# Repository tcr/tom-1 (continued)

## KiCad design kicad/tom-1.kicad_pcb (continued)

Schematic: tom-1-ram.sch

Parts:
J6: Conn_02x08_Top_Bottom; PinSocket_2x09_P2.54mm_Vertical
U22, U28: CY62256; DIP-28_W15.24mm

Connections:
/ADD/stack0: U22.21 (A0); also elsewhere on the board
/ADD/stack1: U22.23 (A1); also elsewhere on the board
/ADD/stack2: U22.24 (A2); also elsewhere on the board
/ADD/stack3: U22.25 (A3); also elsewhere on the board
/ADD/stack4: U22.26 (A4); also elsewhere on the board
/ADD/stack5: U22.1 (A5); also elsewhere on the board
/ADD/stack6: U22.2 (A6); also elsewhere on the board
/ADD/stack7: U22.3 (A7); also elsewhere on the board
/ADD/stack8: U22.4 (A8); also elsewhere on the board
/ADD/stack9: U22.5 (A9); also elsewhere on the board
/ADD/stack10: U22.6 (A10); also elsewhere on the board
/ADD/stack11: U22.7 (A11); also elsewhere on the board
/ADD/stack12: U22.8 (A12); also elsewhere on the board
/ADD/stack13: U22.9 (A13); also elsewhere on the board
/ADD/stack14: U22.10 (A14); also elsewhere on the board
/ADD/tos_bus0: U22.11 (D0); also elsewhere on the board
/ADD/tos_bus1: U22.12 (D1); also elsewhere on the board
/ADD/tos_bus2: U22.13 (D2); also elsewhere on the board
/ADD/tos_bus3: U22.15 (D3); also elsewhere on the board
/ADD/tos_bus4: U22.16 (D4); also elsewhere on the board
/ADD/tos_bus5: U22.17 (D5); also elsewhere on the board
/ADD/tos_bus6: U22.18 (D6); also elsewhere on the board
/ADD/tos_bus7: U22.19 (D7); also elsewhere on the board
/ADD/tos_bus8: U28.11 (D0); also elsewhere on the board
/ADD/tos_bus9: U28.12 (D1); also elsewhere on the board
/ADD/tos_bus10: U28.13 (D2); also elsewhere on the board
/ADD/tos_bus11: U28.15 (D3); also elsewhere on the board
/ADD/tos_bus12: U28.16 (D4); also elsewhere on the board
/ADD/tos_bus13: U28.17 (D5); also elsewhere on the board
/ADD/tos_bus14: U28.18 (D6); also elsewhere on the board
/ADD/tos_bus15: U28.19 (D7); also elsewhere on the board
/RAM/~chip_enable: U28.20 (~CE)
/RAM/~chip_enable~: U22.20 (~CE)
/RAM/~output_enable~: U22.22 (~OE), U28.22 (~OE)
/RAM/~write_enable~: U22.27 (~WE), U28.27 (~WE)
GNDREF: U22.14 (VSS), U28.14 (VSS); also elsewhere on the board
VCC: U22.28 (VCC), U28.28 (VCC); also elsewhere on the board

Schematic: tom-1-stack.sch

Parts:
J8: Conn_02x08_Top_Bottom; PinSocket_2x09_P2.54mm_Vertical
U10, U11: 2KB_SRAM; DIP-24_W10.16mm

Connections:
/ADD/stack0: U10.9 (D0); also elsewhere on the board
/ADD/stack1: U10.10 (D1); also elsewhere on the board
/ADD/stack2: U10.11 (D2); also elsewhere on the board
/ADD/stack3: U10.13 (D3); also elsewhere on the board
/ADD/stack4: U10.14 (D4); also elsewhere on the board
/ADD/stack5: U10.15 (D5); also elsewhere on the board
/ADD/stack6: U10.16 (D6); also elsewhere on the board
/ADD/stack7: U10.17 (D7); also elsewhere on the board
/ADD/stack8: U11.9 (D0); also elsewhere on the board
/ADD/stack9: U11.10 (D1); also elsewhere on the board
/ADD/stack10: U11.11 (D2); also elsewhere on the board
/ADD/stack11: U11.13 (D3); also elsewhere on the board
/ADD/stack12: U11.14 (D4); also elsewhere on the board
/ADD/stack13: U11.15 (D5); also elsewhere on the board
/ADD/stack14: U11.16 (D6); also elsewhere on the board
/ADD/stack15: U11.17 (D7); also elsewhere on the board
/D/R Registers/stack0: U10.8 (A0), U11.8 (A0); also elsewhere on the board
/D/R Registers/stack1: U10.7 (A1), U11.7 (A1); also elsewhere on the board
/D/R Registers/stack2: U10.6 (A2), U11.6 (A2); also elsewhere on the board
/D/R Registers/stack3: U10.5 (A3~), U11.5 (A3~)
/D/R Registers/stack4: U10.4 (A4~), U11.4 (A4~); also elsewhere on the board
/D/R Registers/stack5: U10.3 (A5~), U11.3 (A5~); also elsewhere on the board
/D/R Registers/stack6: U10.2 (A6~), U11.2 (A6~); also elsewhere on the board
/D/R Registers/stack7: U10.1 (A7), U11.1 (A7)
/Stack/a8: U10.23 (A8), U11.23 (A8)
/Stack/~chip_select: U10.18 (~CS), U11.18 (~CS)
/Stack/~output_enable: U10.20 (~OE), U11.20 (~OE)
/Stack/~write_enable: U10.21 (~WE), U11.21 (~WE)
GNDREF: U10.12 (GND~), U10.19 (A10), U10.22 (A9), U11.12 (GND~), U11.19 (A10), U11.22 (A9); also elsewhere on the board
VCC: U10.24 (VCC), U11.24 (VCC); also elsewhere on the board

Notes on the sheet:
STACK: SRAM (2K x 16) with 1.5K unused

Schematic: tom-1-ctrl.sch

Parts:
U4: 74LS573; DIP-20_W7.62mm

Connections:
/Control/output_enable: U4.1 (OE)
/TOS/clk: U4.11 (Load); also elsewhere on the board
GND: U4.10 (GND); also elsewhere on the board
VCC: U4.20 (VCC); also elsewhere on the board

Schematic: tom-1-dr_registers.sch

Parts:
IC4: 74HC697; DIP-20_W7.62mm
J5: Conn_02x08_Top_Bottom; PinSocket_2x09_P2.54mm_Vertical
U6, U16, U17: 74LS697; DIP-20_W7.62mm

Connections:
/D/R Registers/stack0: IC4.18 (QA), U16.18 (QA); also elsewhere on the board
/D/R Registers/stack1: IC4.17 (QB), U16.17 (QB); also elsewhere on the board
/D/R Registers/stack2: IC4.16 (QC), U16.16 (QC); also elsewhere on the board
/D/R Registers/stack4: U6.18 (QA), U17.18 (QA); also elsewhere on the board
/D/R Registers/stack5: U6.17 (QB), U17.17 (QB); also elsewhere on the board
/D/R Registers/stack6: U6.16 (QC), U17.16 (QC); also elsewhere on the board
/D/R Registers/~d_enable: IC4.7 (~ENP), U6.7 (~ENP)
/D/R Registers/~r_enable: U16.7 (~ENP), U17.7 (~ENP)
GNDREF: IC4.10 (GND), U6.10 (GND), U17.10 (GND); also elsewhere on the board
VCC: IC4.13 (~LOAD), IC4.20 (VCC), U6.13 (~LOAD), U6.20 (VCC), U16.13 (~LOAD), U16.20 (VCC), U17.13 (~LOAD), U17.20 (VCC); also elsewhere on the board

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
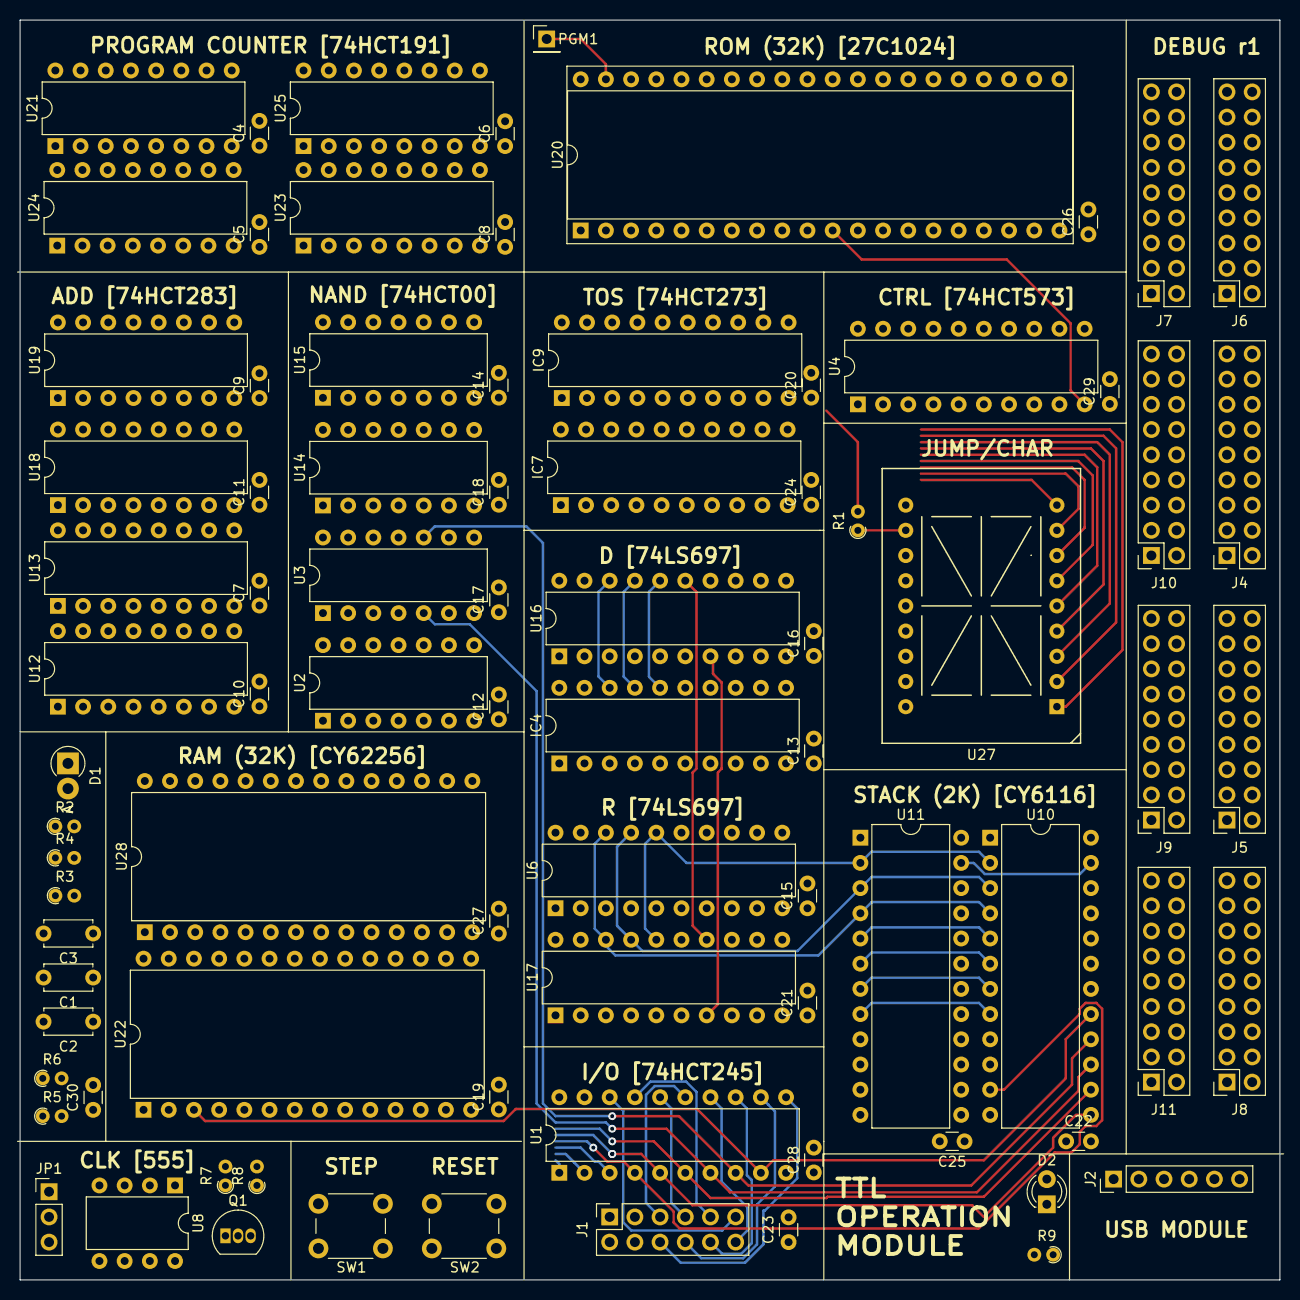
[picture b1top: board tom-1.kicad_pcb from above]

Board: 4 copper layers, 127.0 x 127.0 mm, 83 parts (0 on the bottom side), 132 nets.

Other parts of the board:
PGM1: Conn_01x01_Male; PinHeader_1x01_P2.54mm_Vertical

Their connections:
unnamed 282: PGM1.1; also elsewhere on the board

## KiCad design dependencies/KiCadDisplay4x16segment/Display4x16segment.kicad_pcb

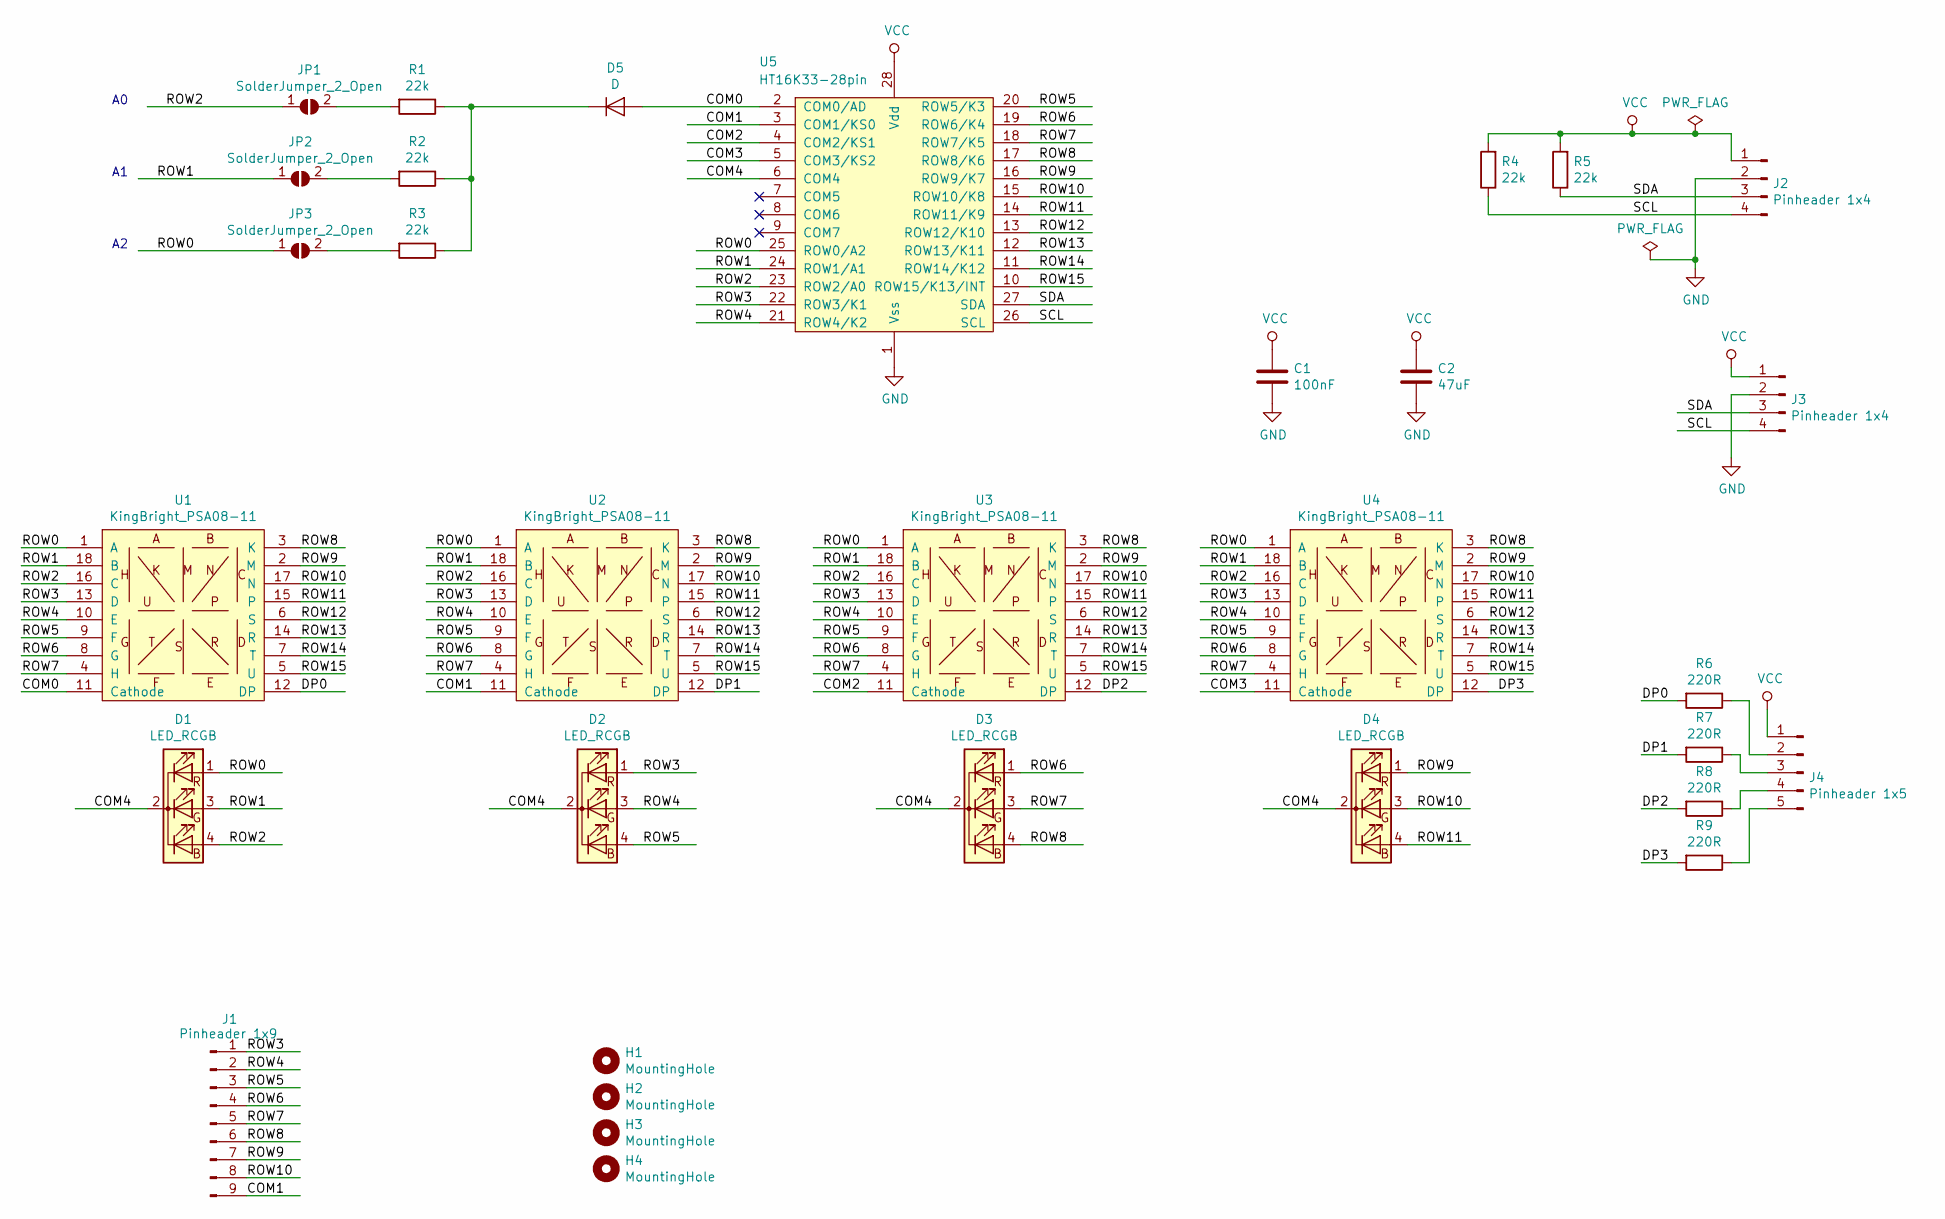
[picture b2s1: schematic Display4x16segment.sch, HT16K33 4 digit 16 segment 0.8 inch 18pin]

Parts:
C1: 100nF; C_0805_HandSoldering
C2: 47uF; C_1206_HandSoldering
D1, D2, D3, D4: LED_RCGB; LED_D5.0mm-4
D5: D; D_SOD-323_HandSoldering
H1, H2, H3, H4: MountingHole; MountingHole_2.2mm_M2_DIN965
J1: Pinheader 1x9; Pin_Header_Straight_1x09_Pitch2.54mm
J2, J3: Pinheader 1x4; Pin_Header_Straight_1x04_Pitch2.54mm
J4: Pinheader 1x5; Pin_Header_Straight_1x05_Pitch2.54mm
JP1, JP2, JP3: SolderJumper_2_Open; SolderJumper-2_P1.3mm_Open_RoundedPad1.0x1.5mm
R1, R2, R3, R4, R5: 22k; R_0805_HandSoldering
R6, R7, R8, R9: 220R; R_0805_HandSoldering
U1, U2, U3, U4: KingBright_PSA08-11; Display08inch16segment
U5: HT16K33-28pin; SOIC-28W_7.5x18.7mm_Pitch1.27mm

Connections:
/COM0: D5.2 (A), U1.11 (Cathode), U5.2 (COM0/AD)
/COM1: J1.9, U2.11 (Cathode), U5.3 (COM1/KS0)
/COM2: U3.11 (Cathode), U5.4 (COM2/KS1)
/COM3: U4.11 (Cathode), U5.5 (COM3/KS2)
/COM4: D1.2 (K), D2.2 (K), D3.2 (K), D4.2 (K), U5.6 (COM4)
/DP0: R6.2, U1.12 (DP)
/DP1: R7.2, U2.12 (DP)
/DP2: R8.2, U3.12 (DP)
/DP3: R9.2, U4.12 (DP)
/ROW0: D1.1 (RA), JP3.1 (A), U1.1 (A), U2.1 (A), U3.1 (A), U4.1 (A), U5.25 (ROW0/A2)
/ROW1: D1.3 (GA), JP2.1 (A), U1.18 (B), U2.18 (B), U3.18 (B), U4.18 (B), U5.24 (ROW1/A1)
/ROW2: D1.4 (BA), JP1.1 (A), U1.16 (C), U2.16 (C), U3.16 (C), U4.16 (C), U5.23 (ROW2/A0)
/ROW3: D2.1 (RA), J1.1, U1.13 (D), U2.13 (D), U3.13 (D), U4.13 (D), U5.22 (ROW3/K1)
/ROW4: D2.3 (GA), J1.2, U1.10 (E), U2.10 (E), U3.10 (E), U4.10 (E), U5.21 (ROW4/K2)
/ROW5: D2.4 (BA), J1.3, U1.9 (F), U2.9 (F), U3.9 (F), U4.9 (F), U5.20 (ROW5/K3)
/ROW6: D3.1 (RA), J1.4, U1.8 (G), U2.8 (G), U3.8 (G), U4.8 (G), U5.19 (ROW6/K4)
/ROW7: D3.3 (GA), J1.5, U1.4 (H), U2.4 (H), U3.4 (H), U4.4 (H), U5.18 (ROW7/K5)
/ROW8: D3.4 (BA), J1.6, U1.3 (K), U2.3 (K), U3.3 (K), U4.3 (K), U5.17 (ROW8/K6)
/ROW9: D4.1 (RA), J1.7, U1.2 (M), U2.2 (M), U3.2 (M), U4.2 (M), U5.16 (ROW9/K7)
/ROW10: D4.3 (GA), J1.8, U1.17 (N), U2.17 (N), U3.17 (N), U4.17 (N), U5.15 (ROW10/K8)
/ROW11: D4.4 (BA), U1.15, U2.15, U3.15, U4.15, U5.14 (ROW11/K9)
/ROW12: U1.6 (S), U2.6 (S), U3.6 (S), U4.6 (S), U5.13 (ROW12/K10)
/ROW13: U1.14 (R), U2.14 (R), U3.14 (R), U4.14 (R), U5.12 (ROW13/K11)
/ROW14: U1.7 (T), U2.7 (T), U3.7 (T), U4.7 (T), U5.11 (ROW14/K12)
/ROW15: U1.5 (U), U2.5 (U), U3.5 (U), U4.5 (U), U5.10 (ROW15/K13/INT)
/SCL: J2.4, J3.4, R4.1, U5.26 (SCL)
/SDA: J2.3, J3.3, R5.1, U5.27 (SDA)
GND: C1.2, C2.2, J2.2, J3.2, U5.1 (Vss)
unnamed: D5.1 (K), R1.1, R2.1, R3.1
unnamed: J4.2, R6.1
unnamed: J4.3, R7.1
unnamed: J4.4, R8.1
unnamed: J4.5, R9.1
unnamed: JP1.2 (B), R1.2
unnamed: JP2.2 (B), R2.2
unnamed: JP3.2 (B), R3.2
VCC: C1.1, C2.1, J2.1, J3.1, J4.1, R4.2, R5.2, U5.28 (Vdd)

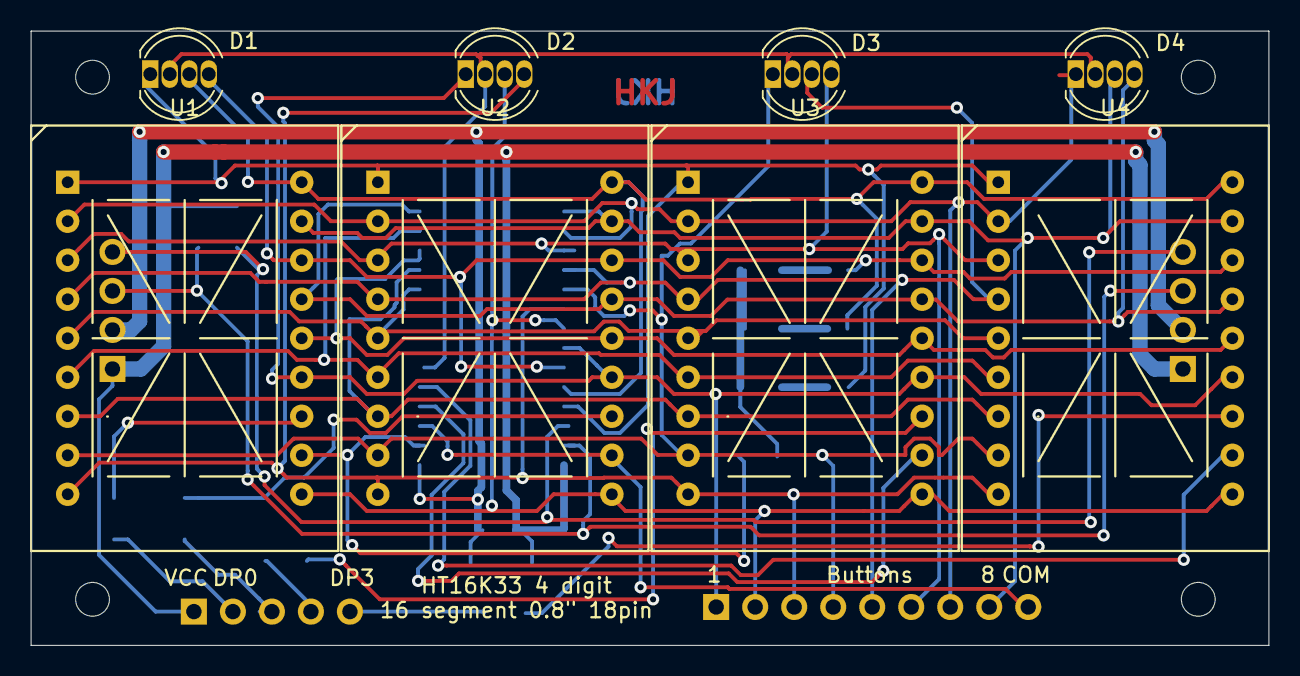
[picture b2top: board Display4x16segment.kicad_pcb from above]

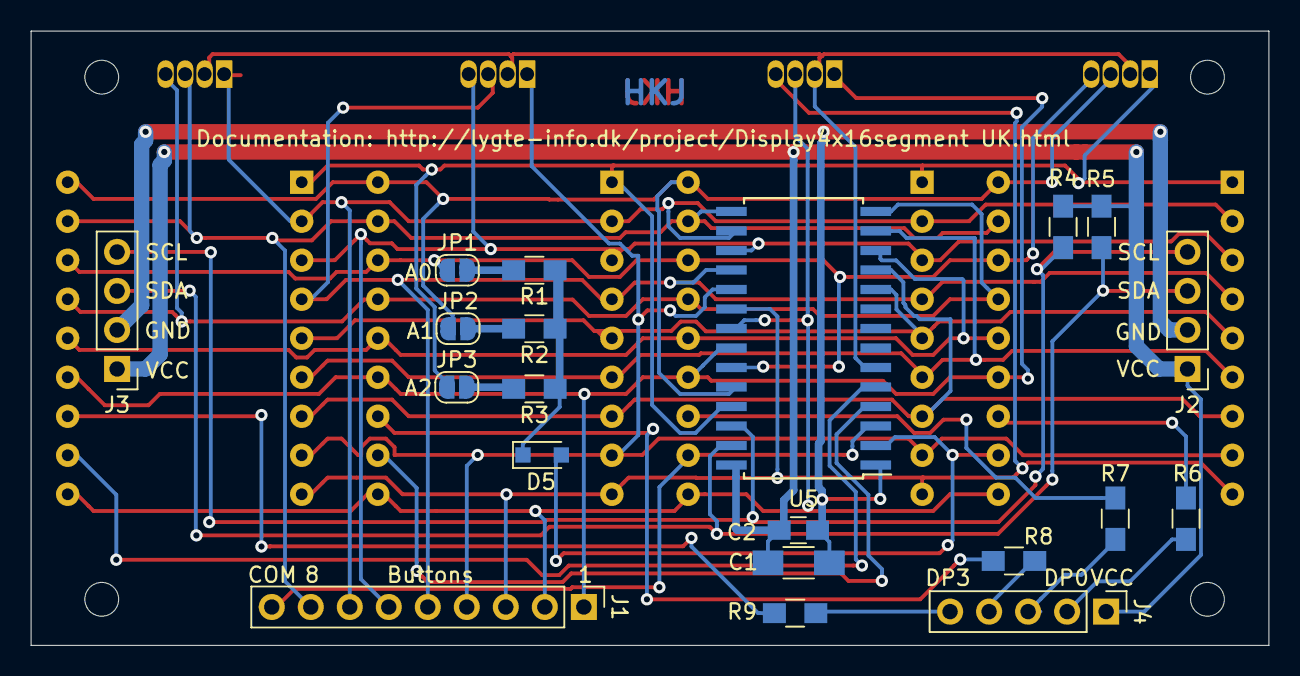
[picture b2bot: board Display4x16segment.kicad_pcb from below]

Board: 2 copper layers, 80.6 x 40.0 mm, 32 parts (20 on the bottom side), 37 nets.

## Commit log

2020-05-26 Next level
2020-06-14 Lots of Digital work
2020-06-16 sorta working jump logic
2020-06-17 store works
2020-06-17 NEXT_GEN_WRITE
2020-06-17 Better version of store
2020-06-18 runs tomscii
2020-06-18 make instr 0 clear TOS
2020-06-20 Finalized automated tets
2020-06-21 some progress to pax
2020-06-21 269 hooked up
2020-06-22 It somehow works
2020-06-22 good
2020-06-23 Quick fix for the jump logic
2020-06-23 Adds LEDs to CTRL
2020-06-23 Latest layout
2020-06-24 better jump caching
2020-06-25 Full tests
2020-07-01 More modifications
2020-07-10 Public release
2020-07-10 README
2020-07-10 Need to support sbrs with branch0[+5] or something
2020-07-24 Adds emulation file
2020-07-30 Functional emulated multiply
2020-08-11 Adds 6502 experiments
2020-08-11 Removes outdated screenshots
2020-08-11 Removes backup files
2020-08-11 Adds Hackaday link
